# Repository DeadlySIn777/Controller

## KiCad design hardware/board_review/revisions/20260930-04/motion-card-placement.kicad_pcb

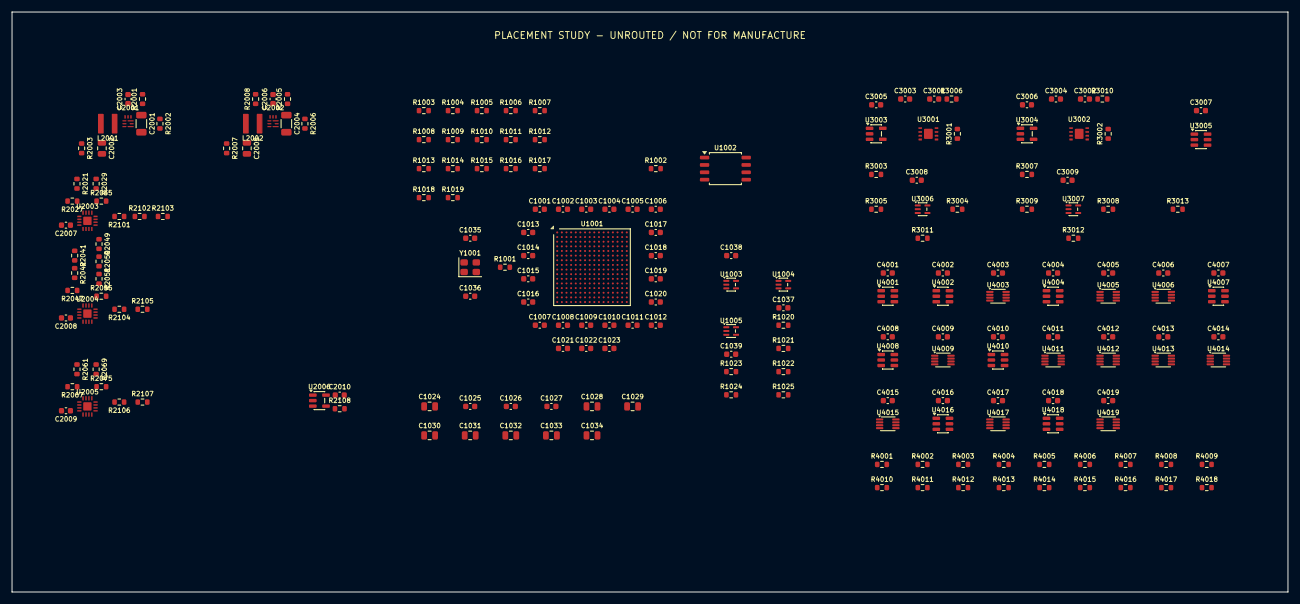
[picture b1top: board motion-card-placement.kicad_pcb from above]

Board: 6 copper layers, 220.0 x 100.0 mm, 203 parts (0 on the bottom side), 103 nets, no tracks yet.

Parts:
C1001, C1002, C1003, C1004, C1005, C1006, C1007, C1008, C1009, C1010, C1011, C1012, C1013, C1014, C1015, C1016, C1017, C1018, C1019, C1020, C1021, C1022, C1023, C1035, C1038: 885012206046; C_0603_1608Metric
C1024, C1028, C1029, C1030, C1031, C1032, C1033, C1034: 885012207053; C_0805_2012Metric
C1025, C1026, C1027, C1036, C1039: 885012206052; C_0603_1608Metric
C1037: 885012206040; C_0603_1608Metric
C2001, C2004: C3216X7R1E106K160AB; C_1206_3216Metric
C2002, C2005: C2012X7S1A226M125AC; C_0805_2012Metric
C2003, C2006: GRM1885C1H682JA01D; C_0603_1608Metric
C2007, C2008, C2009, C2010, C3003, C3004, C3005, C3006, C3007, C3008, C3009, C4001, C4002, C4003, C4004, C4005, C4006, C4007, C4008, C4009, C4010, C4011, C4012, C4013, C4014, C4015, C4016, C4017, C4018, C4019: GRM188R71E104KA01D; C_0603_1608Metric
C3001, C3002: CL10C332JB8NNNC; C_0603_1608Metric
L2001: XGL4020-222MEC; XGL4020
L2002: XGL4020-102MEC; XGL4020
R1001, R1002: CRCW060333R0FKEA; R_0603_1608Metric
R1003, R1004, R1005, R1006, R1007, R1008, R1009, R1010, R1011, R1012, R1013, R1014, R1015, R1016, R1017, R1018, R1019, R1022, R1023, R1024, R1025, R2002, R2006, R2103, R2105, R3001, R3002, R4008, R4009, R4010, R4011, R4012, R4013, R4014, R4015, R4016, R4017, R4018: CRCW060310K0FKEA; R_0603_1608Metric
R1020, R2106: CRCW060347K0FKEA; R_0603_1608Metric
R1021: CRCW06031K00FKEA; R_0603_1608Metric
R2001: CRCW060376K8FKEA; R_0603_1608Metric
R2003, R2007, R3006, R3008, R3009, R3010, R3011, R3012: CRCW0603100KFKEA; R_0603_1608Metric
R2005: CRCW060332K4FKEA; R_0603_1608Metric
R2008: CRCW0603301KFKEA; R_0603_1608Metric
R2021: PLT0603Z8792LST1; R_0603_1608Metric
R2027, R2035, R2067, R2075: PLT0603Z1002LST1; R_0603_1608Metric
R2029: PLT0603Z9212LST1; R_0603_1608Metric
R2041: PLT0603Z1071LST1; R_0603_1608Metric
R2042: PLT0603Z2610LST1; R_0603_1608Metric
R2047, R2055: PLT0603Z1001LST1; R_0603_1608Metric
R2049: PLT0603Z1151LST1; R_0603_1608Metric
R2050: PLT0603Z3160LST1; R_0603_1608Metric
R2051: CRCW06034R02FKEA; R_0603_1608Metric
R2061: PLT0603Z5452LST1; R_0603_1608Metric
R2069: PLT0603Z5752LST1; R_0603_1608Metric
R2101, R2102: CRCW06033K30FKEA; R_0603_1608Metric
R2104: CRCW06036K80FKEA; R_0603_1608Metric
R2107: CRCW0603470KFKEA; R_0603_1608Metric
R2108, R3003, R3004, R3005, R3007, R3013, R4001, R4002, R4003, R4004, R4005, R4006, R4007: CRCW06034K70FKEA; R_0603_1608Metric
U1001: T20F256I4; T20F256_Efinix_NSMD
U1002: W25Q32JVSSIQ; SOIC-8_5.3x5.3mm_P1.27mm
U1003, U1005, U3006, U3007: SN74LVC1G08DCKR; SOT-353_SC-70-5
U1004: 74LVC1G17GW; SOT-353_SC-70-5
U2001, U2002: TPS62901RPJR; TPS62901_RPJ9
U2003, U2004, U2005: LTC2962HUD#TRPBF; LTC2962_UD16
U2006: SN74LVC1G17DBVR; SOT-23-5
U3001, U3002: TPS3851G18SDRBT; TPS3851_DRB8
U3003, U3004: SN74LVC1G34DBVR; SOT-23-5
U3005: SN74LVC2G17DBVR; SOT-23-6
U4001, U4002, U4004, U4007, U4008, U4010: SN74LVC1G11DBVR; SOT-23-6
U4003, U4009, U4019: SN74LVC2G08DCUR; VSSOP-8_2.3x2mm_P0.5mm
U4005, U4006, U4011, U4012, U4013, U4014, U4015: SN74LVC2G74DCUR; VSSOP-8_2.3x2mm_P0.5mm
U4016, U4018: SN74LVC2G04DBVR; SOT-23-6
U4017: SN74LVC2G32DCUR; VSSOP-8_2.3x2mm_P0.5mm
Y1001: ASE-50.000MHZ-L-C-T; Oscillator_SMD_Abracon_ASE-4Pin_3.2x2.5mm

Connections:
/CORE_1V2: C1001.1, C1002.1, C1003.1, C1004.1, C1005.1, C1006.1, C1007.1, C1008.1, C1009.1, C1024.1, C1025.1, C1026.1, C1027.1, C2002.1, L2001.2, R2003.1, R2041.1, R2049.1, U1001.E9, U1001.F7, U1001.F8, U1001.F9, U1001.G11, U1001.J6, U1001.J7, U1001.K9, U1001.K11, U2001.3
/FPGA_CRESET_N: R2108.1, R4008.1, U1003.1, U2006.4, U4001.1, U4019.1, U4019.5
/FPGA_ENDPOINT_READY: R1023.1, R4001.1, U1001.C4, U4003.6, U4004.6
/FPGA_MOTION_REQUEST: R1024.1, R3003.1, U1001.B3, U3006.1, U4005.1, U4007.3
/FPGA_OUTPUT_REQUEST: R3004.1, U3007.1, U4006.1, U4008.3
/FPGA_PROGRESS_M: R1025.1, R3005.1, U1001.E4, U3003.2
/FPGA_USER_RESET_N: R3013.1, R4009.1, U1001.D5, U1005.4, U3006.2, U3007.2, U4001.3
/IO_3V3: C1010.1, C1011.1, C1012.1, C1013.1, C1014.1, C1015.1, C1016.1, C1017.1, C1018.1, C1019.1, C1020.1, C1021.1, C1022.1, C1023.1, C1028.1, C1029.1, C1030.1, C1031.1, C1032.1, C1033.1, C1034.1, C1035.1, C1036.1, C1037.1, C1038.1, C2005.1, C2010.1, C3003.1, C3004.1, C3005.1, C3006.1, C3007.1, C3008.1, C3009.1, C4001.1, C4002.1, C4003.1, C4004.1, C4005.1, C4006.1, C4007.1, C4008.1, C4009.1, C4010.1, C4011.1, C4012.1, C4013.1, C4014.1, C4015.1, C4016.1, C4017.1, C4018.1, C4019.1, L2002.2, R1003.1, R1004.1, R1005.1, R1006.1, R1007.1, R1008.1, R1009.1, R1010.1, R1011.1, R1012.1, R1013.1, R1014.1, R1015.1, R1016.1, R1017.1, R1020.1, R2007.1, R2061.1, R2069.1, R3001.1, R3002.1, U1001.E10, U1001.F6, U1001.F10, U1001.F11, U1001.G6, U1001.H6, U1001.H7, U1001.J10, U1001.J11, U1001.K6, U1001.L6, U1001.L7, U1001.L10, U1001.L11, U1002.8, U1003.5, U1004.5, U1005.5, U2002.3, U2006.5, U3001.1, U3002.1, U3003.5, U3004.5, U3005.5, U3006.5, U3007.5, U4001.5, U4002.5, U4003.8, U4004.5, U4005.2, U4005.7, U4005.8, U4006.2, U4006.7, U4006.8, U4007.5, U4008.5, U4009.8, U4010.5, U4011.2, U4011.7, U4011.8, U4012.2, U4012.7, U4012.8, U4013.2, U4013.7, U4013.8, U4014.7, U4014.8, U4015.7, U4015.8, U4016.5, U4017.8, U4018.5, U4019.8, Y1001.1, Y1001.4
/LOGIC_GND: C1001.2, C1002.2, C1003.2, C1004.2, C1005.2, C1006.2, C1007.2, C1008.2, C1009.2, C1010.2, C1011.2, C1012.2, C1013.2, C1014.2, C1015.2, C1016.2, C1017.2, C1018.2, C1019.2, C1020.2, C1021.2, C1022.2, C1023.2, C1024.2, C1025.2, C1026.2, C1027.2, C1028.2, C1029.2, C1030.2, C1031.2, C1032.2, C1033.2, C1034.2, C1035.2, C1036.2, C1037.2, C1038.2, C1039.2, C2001.2, C2002.2, C2003.2, C2004.2, C2005.2, C2006.2, C2007.2, C2008.2, C2009.2, C2010.2, C3001.2, C3002.2, C3003.2, C3004.2, C3005.2, C3006.2, C3007.2, C3008.2, C3009.2, C4001.2, C4002.2, C4003.2, C4004.2, C4005.2, C4006.2, C4007.2, C4008.2, C4009.2, C4010.2, C4011.2, C4012.2, C4013.2, C4014.2, C4015.2, C4016.2, C4017.2, C4018.2, C4019.2, R1018.2, R1019.2, R1021.2, R1023.2, R1024.2, R1025.2, R2001.2, R2002.2, R2003.2, R2005.2, R2006.2, R2007.2, R2008.2, R2027.2, R2035.2, R2047.2, R2055.2, R2067.2, R2075.2, R2103.2, R2105.2, R2107.2, R2108.2, R3003.2, R3004.2, R3005.2, R3006.2, R3007.2, R3008.2, R3009.2, R3010.2, R3011.2, R3012.2, R3013.2, R4001.2, R4002.2, R4003.2, R4004.2, R4005.2, R4006.2, R4007.2, R4008.2, R4009.2, R4010.2, R4011.2, R4012.2, R4013.2, R4014.2, R4015.2, R4016.2, R4017.2, R4018.2, U1001.A1, U1001.A5, U1001.A12, U1001.A16, U1001.D2, U1001.D15, U1001.G7, U1001.G8, U1001.G9, U1001.G10, U1001.H8, U1001.H9, U1001.H10, U1001.H11, U1001.J1, U1001.J8, U1001.J9, U1001.J16, U1001.K7, U1001.K8, U1001.K10, U1001.L8, U1001.L9, U1001.N2, U1001.N15, U1001.R7, U1001.R10, U1001.T1, U1001.T4, U1001.T13, U1001.T16, U1002.4, U1003.3, U1004.3, U1005.3, U2001.4, U2001.9, U2002.4, U2003.3, U2003.7, U2003.11, U2003.17, U2004.3, U2004.7, U2004.11, U2004.17, U2005.3, U2005.7, U2005.11, U2005.17, U2006.3, U3001.4, U3001.9, U3002.4, U3002.9, U3003.3, U3004.3, U3005.2, U3006.3, U3007.3, U4001.2, U4002.2, U4003.4, U4004.2, U4005.4, U4006.4, U4007.2, U4008.2, U4009.4, U4010.2, U4011.4, U4012.4, U4013.4, U4014.4, U4015.4, U4016.2, U4017.4, U4018.2, U4019.4, Y1001.2
/RAW_INHIBIT_N: U1001.A2, U4003.5, U4003.7, U4007.6
/TX_PERMIT: R4015.1, U1001.E6, U4007.4, U4009.5, U4010.1, U4011.6
/WD_M_OK: R3009.1, U3005.6, U4003.2, U4016.1
/WD_M_SET1_BUF: R3011.1, U3001.5, U3006.4, U4017.2
/WD_O_OK: R3010.1, U3005.4, U4004.3, U4009.2, U4016.3
/WD_O_SET1_BUF: R3012.1, U3002.5, U3007.4, U4017.6
/fpga_core/FPGA_CDONE: R1003.2, R1022.1, U1001.R1
/fpga_core/FPGA_CFG_CBSEL0: R1018.1, U1001.C7
/fpga_core/FPGA_CFG_CBSEL1: R1019.1, U1001.D7
/fpga_core/FPGA_CFG_CBUS0: R1009.2, U1001.K13
/fpga_core/FPGA_CFG_CBUS1: R1008.2, U1001.L14
/fpga_core/FPGA_CFG_CBUS2: R1007.2, U1001.R16
/fpga_core/FPGA_CFG_CSI: R1004.2, U1001.N3
/fpga_core/FPGA_CFG_NSTATUS: R1017.2, U1001.B8
/fpga_core/FPGA_CFG_TEST_N: R1005.2, U1001.L12
/fpga_core/FPGA_CLK_50M: R1001.2, U1001.H3
/fpga_core/FPGA_CLK_SOURCE: R1001.1, Y1001.3
/fpga_core/FPGA_FLASH_CCK: R1002.2, U1002.6
/fpga_core/FPGA_FLASH_CCK_SOURCE: R1002.1, U1001.M3
/fpga_core/FPGA_FLASH_CS_N: R1006.2, U1001.P3, U1002.1
/fpga_core/FPGA_FLASH_IO2: R1014.2, U1002.3
/fpga_core/FPGA_FLASH_IO3: R1015.2, U1002.7
/fpga_core/FPGA_FLASH_MISO: U1001.N1, U1002.2
/fpga_core/FPGA_FLASH_MOSI: U1001.L3, U1002.5
/fpga_core/FPGA_JTAG_TCK: R1010.2, U1001.M2
/fpga_core/FPGA_JTAG_TDI: R1011.2, U1001.K5
/fpga_core/FPGA_JTAG_TDO: R1013.2, U1001.L5
/fpga_core/FPGA_JTAG_TMS: R1012.2, U1001.M1
/fpga_core/FPGA_LOCAL_RESET_N: R1020.2, R1021.1, U1001.P1, U1003.4
/fpga_core/FPGA_SERVICE_RUN_N: R1016.2, U1003.2, U1005.2
/fpga_core/FPGA_USER_RESET_DELAYED: U1004.4, U1005.1
/fpga_core/FPGA_USER_RESET_RC: C1039.1, R1022.2, U1004.2
/mc_local_power/CORE_1V2_EN: R2002.1, R2102.2, R2103.1, U2001.5
/mc_local_power/CORE_1V2_MODE: R2001.1, U2001.7
/mc_local_power/CORE_1V2_OV_SENSE: R2051.2, R2055.1, U2004.15
/mc_local_power/CORE_1V2_SS: C2003.1, U2001.8
/mc_local_power/CORE_1V2_SW: L2001.1, U2001.2
/mc_local_power/CORE_1V2_UV_SENSE: R2042.2, R2047.1, U2004.16
/mc_local_power/CORE_5V: C2001.1, C2004.1, C2007.1, C2008.1, C2009.1, R2021.1, R2029.1, R2101.1, R2104.1, R2106.1, U2001.6, U2002.6, U2003.1, U2003.2, U2003.4, U2003.10, U2003.13, U2003.14, U2004.1, U2004.4, U2004.10, U2004.13, U2004.14, U2005.1, U2005.4, U2005.10, U2005.13, U2005.14
/mc_local_power/CORE_5V_OV_SENSE: R2029.2, R2035.1, U2003.15
/mc_local_power/CORE_5V_UV_SENSE: R2021.2, R2027.1, U2003.16
/mc_local_power/IO_3V3_EN: R2006.1, R2104.2, R2105.1, U2002.5, U2004.12, U2005.2
/mc_local_power/IO_3V3_MODE: R2005.1, U2002.7
/mc_local_power/IO_3V3_OV_SENSE: R2069.2, R2075.1, U2005.15
/mc_local_power/IO_3V3_SS: C2006.1, U2002.8
/mc_local_power/IO_3V3_SW: L2002.1, U2002.2
/mc_local_power/IO_3V3_UV_SENSE: R2061.2, R2067.1, U2005.16
/mc_local_power/IO_3V3_VSET: R2008.1, U2002.9
/mc_local_power/MC_RAILS_OK_5V: R2106.2, R2107.1, U2005.12, U2006.2
/mc_local_power/MC_SEQ_5V_OK: R2101.2, R2102.1, U2003.12, U2004.2
/mc_local_power/MC_SEQ_OV2_1: R2049.2, R2050.1
/mc_local_power/MC_SEQ_OV2_2: R2050.2, R2051.1
/mc_local_power/MC_SEQ_REF1: U2003.5, U2003.6, U2003.8, U2003.9
/mc_local_power/MC_SEQ_REF2: U2004.5, U2004.6, U2004.8, U2004.9
/mc_local_power/MC_SEQ_REF3: U2005.5, U2005.6, U2005.8, U2005.9
/mc_local_power/MC_SEQ_UV2_1: R2041.2, R2042.1
/mc_permission/ARM_M_Q: U4005.5, U4007.1
/mc_permission/ARM_O_Q: U4006.5, U4008.1
/mc_permission/BANK_B_BUFFER_ENABLE_QUALIFIED: R4014.1, U4013.6
/mc_permission/BASE_FIRST: U4001.4, U4002.1
/mc_permission/BASE_OK: U4002.4, U4003.1, U4004.1, U4009.1
/mc_permission/DIC_OK_QUALIFIED: R4010.1, U4001.6
/mc_permission/EXT_PERMIT_3V3: R4011.1, U4002.3
/mc_permission/LATCH_CLEAR_M_N: U4003.3, U4005.6
/mc_permission/LATCH_CLEAR_O_N: U4004.4, U4006.6
/mc_permission/OPI_REARM_BOE: R4004.1, U4013.1
/mc_permission/OPI_REARM_OUT: R4003.1, U4012.1
/mc_permission/OPI_REARM_TX: R4002.1, U4011.1
/mc_permission/OUTPUT_RAW_OK: U4008.6, U4009.7
/mc_permission/OUT_PERMIT: R4016.1, U4008.4, U4010.3, U4012.6
/mc_permission/PERMIT_OUT_DRIVE: R4018.1, U4009.3
/mc_permission/PERMIT_OUT_REQ: R4007.1, U4009.6
/mc_permission/PROCESS_PERMIT_EXT_3V3: R4013.1, U4010.6
/mc_permission/PROC_PERMIT: R4017.1, U4010.4
/mc_permission/TAMPER_CLEAR_N: R4012.1, U4002.6
/mc_permission/WD_M_FALL_CLK: U4014.1, U4016.6
/mc_permission/WD_M_RECORD_CLEAR_N: U4018.6, U4019.2
/mc_permission/WD_M_TRIP_CLEAR_N: U4014.6, U4019.7
/mc_permission/WD_M_TRIP_D: U4014.2, U4017.7
/mc_permission/WD_M_TRIP_Q: U4014.5, U4017.1
/mc_permission/WD_O_FALL_CLK: U4015.1, U4016.4
/mc_permission/WD_O_RECORD_CLEAR_N: U4018.4, U4019.6
/mc_permission/WD_O_TRIP_CLEAR_N: U4015.6, U4019.3
/mc_permission/WD_O_TRIP_D: U4015.2, U4017.3
/mc_permission/WD_O_TRIP_Q: U4015.5, U4017.5
/mc_permission/WD_REARM_M: R4005.1, U4018.1
/mc_permission/WD_REARM_O: R4006.1, U4018.3
/watchdog_conditioning/FPGA_PROGRESS_O: R3007.1, U3004.2
/watchdog_conditioning/WD_M_CWD: C3001.1, U3001.2
/watchdog_conditioning/WD_M_HEALTH_RAW: R3001.2, U3001.7, U3001.8, U3005.1
/watchdog_conditioning/WD_M_WDI_BUF: R3006.1, U3001.6, U3003.4
/watchdog_conditioning/WD_O_CWD: C3002.1, U3002.2
/watchdog_conditioning/WD_O_HEALTH_RAW: R3002.2, U3002.7, U3002.8, U3005.3
/watchdog_conditioning/WD_O_WDI_BUF: R3008.1, U3002.6, U3004.4
